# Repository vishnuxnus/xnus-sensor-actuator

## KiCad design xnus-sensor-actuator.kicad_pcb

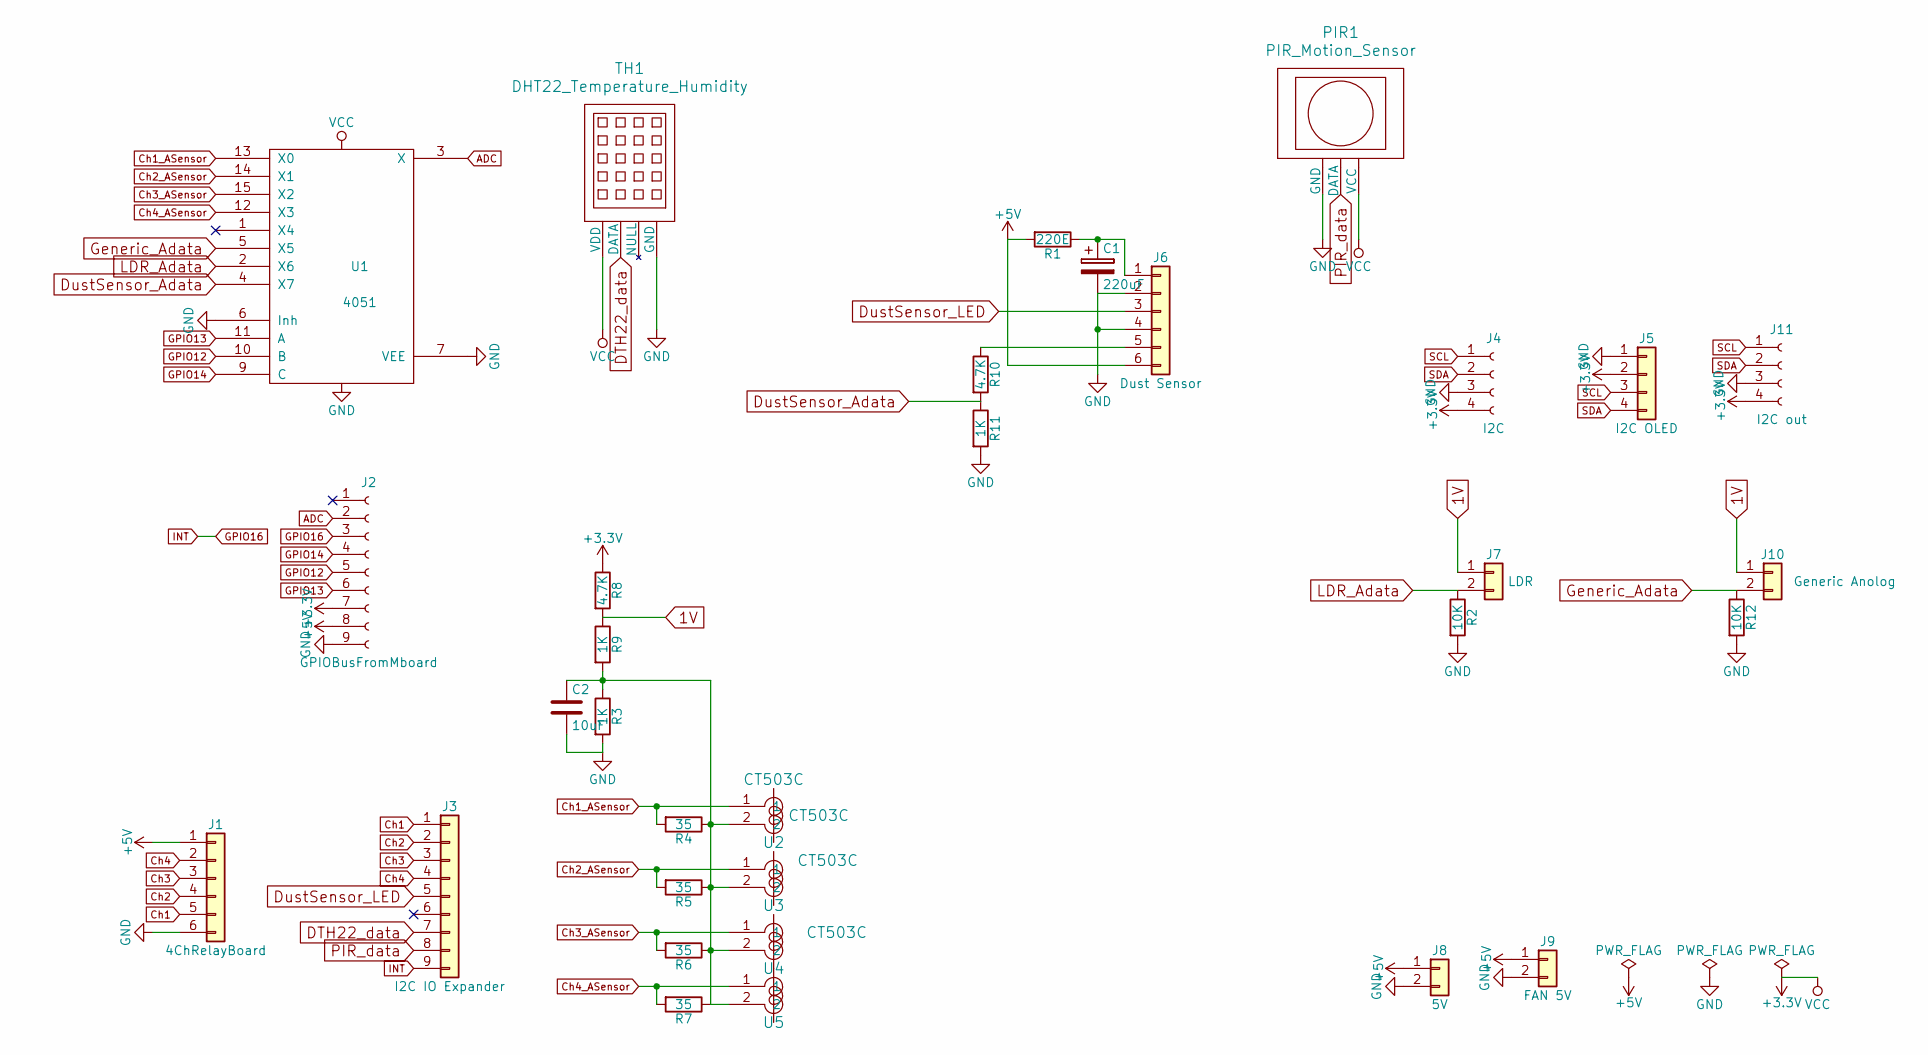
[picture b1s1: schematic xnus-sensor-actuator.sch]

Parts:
C1: 220uF; CP_Radial_D6.3mm_P2.50mm
C2: 10uF; CP_Radial_D6.3mm_P2.50mm
J1: 4ChRelayBoard; Pin_Header_Straight_1x06_Pitch2.54mm
J2: GPIOBusFromMboard; Pin_Header_Straight_1x09_Pitch2.54mm
J3: I2C IO Expander; Pin_Header_Straight_1x09_Pitch2.54mm
J4: I2C; JST_EH_B04B-EH-A_04x2.50mm_Straight
J5: I2C OLED; JST_EH_B04B-EH-A_04x2.50mm_Straight
J6: Dust Sensor; JST_EH_B06B-EH-A_06x2.50mm_Straight
J7: LDR; JST_EH_B02B-EH-A_02x2.50mm_Straight
J8: 5V; JST_EH_B02B-EH-A_02x2.50mm_Straight
J9: FAN 5V; JST_EH_B02B-EH-A_02x2.50mm_Straight
J10: Generic Anolog; JST_EH_B02B-EH-A_02x2.50mm_Straight
J11: I2C out; JST_EH_B04B-EH-A_04x2.50mm_Straight
PIR1: PIR_Motion_Sensor; JST_EH_B03B-EH-A_03x2.50mm_Straight
R1: 220E; R_Axial_DIN0207_L6.3mm_D2.5mm_P5.08mm_Vertical
R2, R12: 10K; R_Axial_DIN0207_L6.3mm_D2.5mm_P5.08mm_Vertical
R3, R9, R11: 1K; R_Axial_DIN0207_L6.3mm_D2.5mm_P5.08mm_Vertical
R4, R5, R6, R7: 35; R_Axial_DIN0207_L6.3mm_D2.5mm_P7.62mm_Horizontal
R8, R10: 4.7K; R_Axial_DIN0207_L6.3mm_D2.5mm_P5.08mm_Vertical
TH1: DHT22_Temperature_Humidity
U1: 4051; DIP-16_W7.62mm_LongPads
U2, U3, U4, U5: CT503C

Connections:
1V: J7.1, J10.1, R8.2, R9.1
+3V3: J2.7, J4.4, J5.2, J11.4, PIR1.3 (VCC), R8.1, TH1.1 (VDD), U1.16 (VDD)
+5V: J1.1, J2.8, J6.6, J8.1, J9.1, R1.2
ADC: J2.2, U1.3 (X)
Ch1: J1.5, J3.1
Ch1_ASensor: R4.2, U1.13 (X0), U2.1
Ch2: J1.4, J3.2
Ch2_ASensor: R5.2, U1.14 (X1), U3.1
Ch3: J1.3, J3.3
Ch3_ASensor: R6.2, U1.15 (X2), U4.1
Ch4: J1.2, J3.4
Ch4_ASensor: R7.2, U1.12 (X3), U5.1
DTH22_data: J3.7, TH1.2 (DATA)
DustSensor_Adata: R10.2, R11.1, U1.4 (X7)
DustSensor_LED: J3.5, J6.3
GND: C1.2, C2.2, J1.6, J2.9, J4.3, J5.1, J6.2, J6.4, J8.2, J9.2, J11.3, PIR1.1 (GND), R2.2, R3.2, R11.2, R12.2, TH1.4 (GND), U1.6 (Inh), U1.7 (VEE), U1.8 (VSS)
GPIO12: J2.5, U1.10 (B)
GPIO13: J2.6, U1.11 (A)
GPIO14: J2.4, U1.9 (C)
GPIO16: J2.3, J3.9
Generic_Adata: J10.2, R12.1, U1.5 (X5)
LDR_Adata: J7.2, R2.1, U1.2 (X6)
unnamed: C1.1, J6.1, R1.1
unnamed: C2.1, R3.1, R4.1, R5.1, R6.1, R7.1, R9.2, U2.2, U3.2, U4.2, U5.2
unnamed: J6.5, R10.1
PIR_data: J3.8, PIR1.2 (DATA)
SCL: J4.1, J5.3, J11.1
SDA: J4.2, J5.4, J11.2

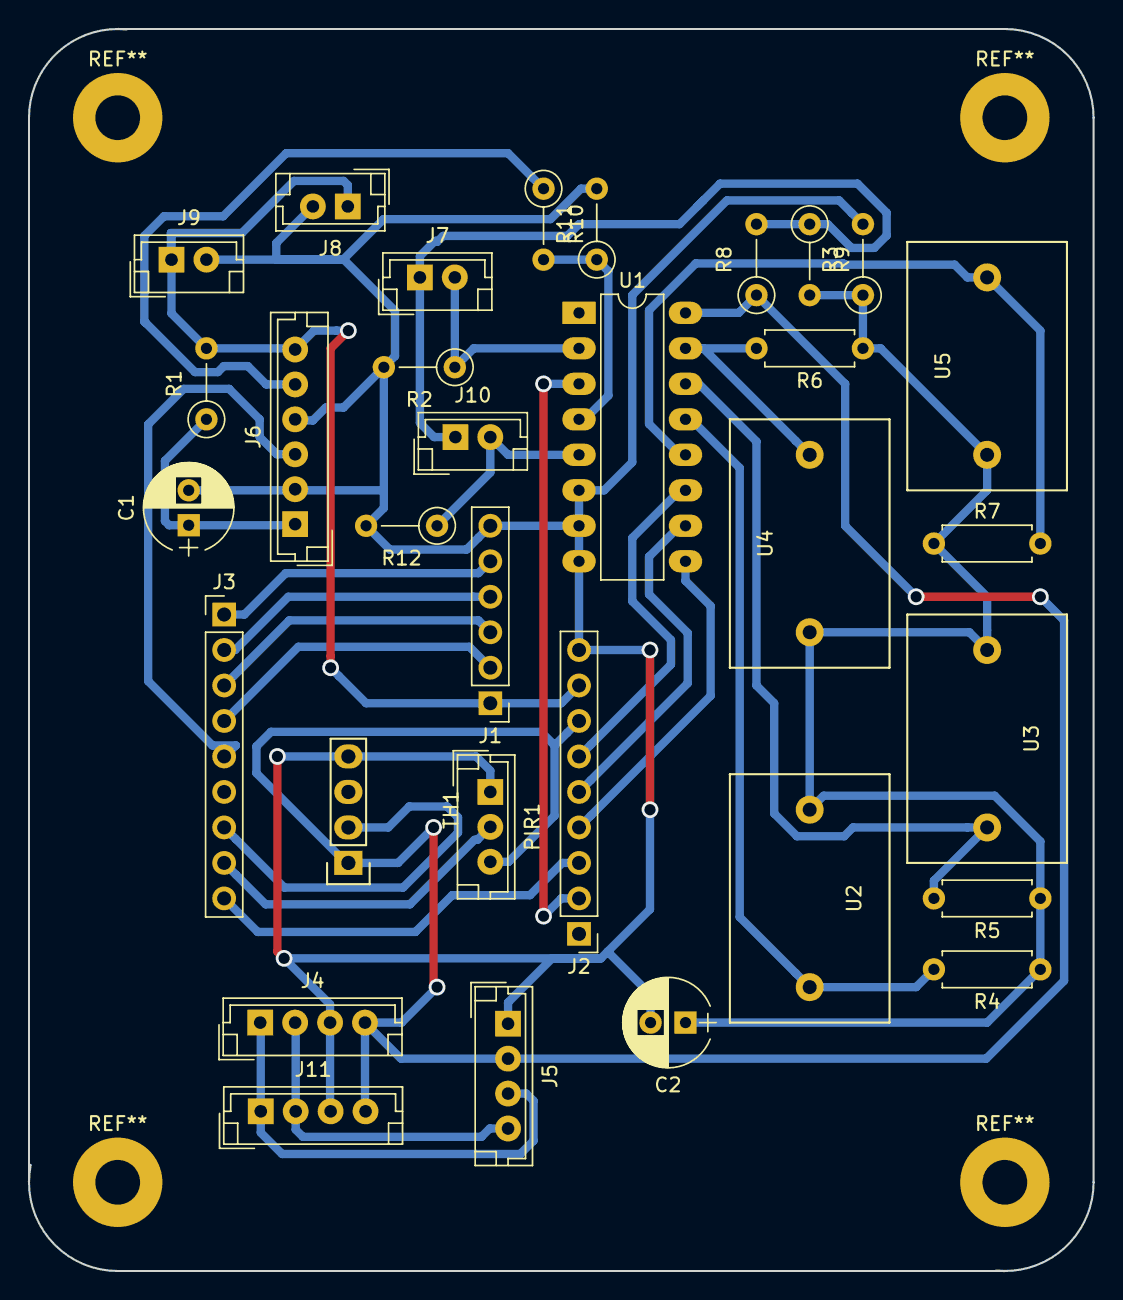
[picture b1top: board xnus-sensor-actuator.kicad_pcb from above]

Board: 2 copper layers, 76.2 x 88.9 mm, 32 parts (0 on the bottom side), 28 nets.
